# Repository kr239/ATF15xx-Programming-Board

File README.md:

# ATF15xx Programming Board

A simple PCB that will allow you to program 44-pin PLCC ATF15xx series CPLD's using an Byte Blaster or other similar ISP cable.

J2 is the power input, Max 9v DC

# Bill of Materials

-= COMING SOON =-

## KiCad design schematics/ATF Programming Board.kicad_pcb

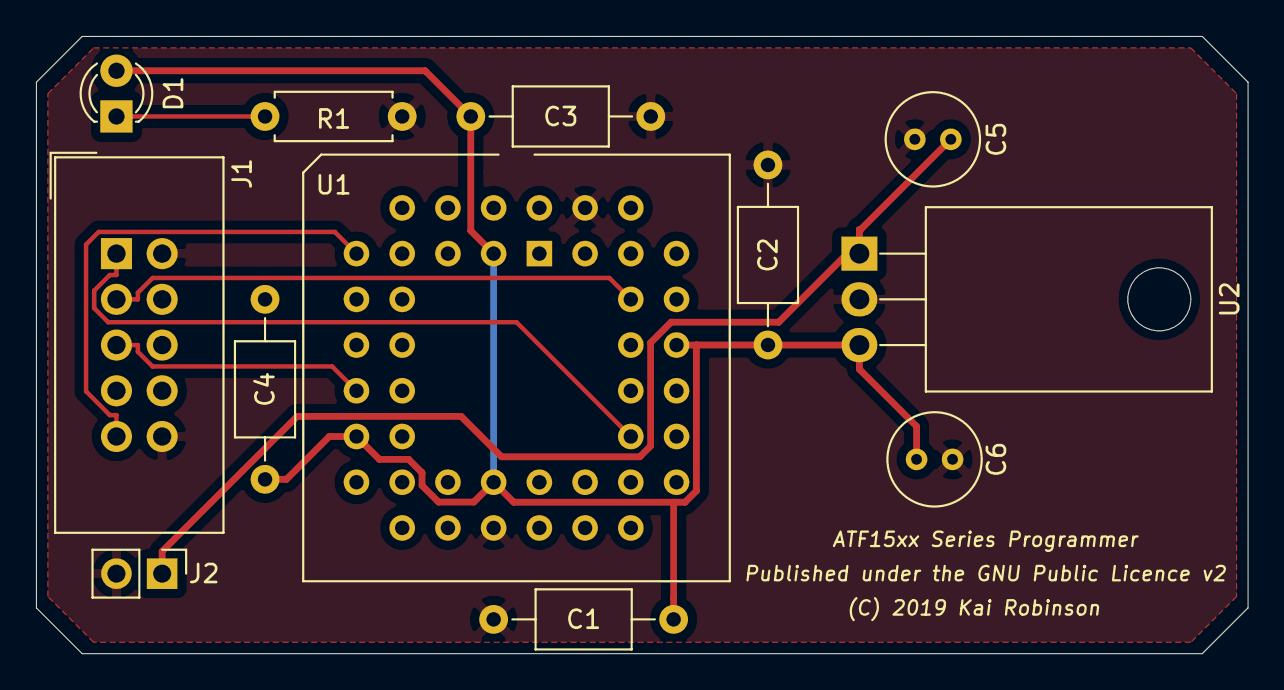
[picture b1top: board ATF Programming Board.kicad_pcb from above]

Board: 2 copper layers, 67.3 x 34.3 mm, 12 parts (0 on the bottom side), 8 nets.

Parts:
C1, C2, C3, C4: 0.1uF; C_Axial_L5.1mm_D3.1mm_P10.00mm_Horizontal
C5: 0.33uF; C_Radial_D5.0mm_H5.0mm_P2.00mm
C6: 0.1uF; C_Radial_D5.0mm_H5.0mm_P2.00mm
D1: LED_ALT; LED_D3.0mm
J1: AVR-JTAG-10; IDC-Header_2x05_P2.54mm_Vertical
J2: Conn_01x02_Male; PinHeader_1x02_P2.54mm_Vertical
R1: 1k; R_Axial_DIN0207_L6.3mm_D2.5mm_P7.62mm_Horizontal
U1: ATF1502ASV-15JU44; PLCC-44_THT-Socket
U2: LM7805_TO220; TO-220-3_Horizontal_TabDown

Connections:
/gnd: C1.1, C2.2, C3.2, C4.1, C5.2, C6.2, J1.2, J1.10, J2.2, R1.1, U1.10, U1.22, U1.30, U1.42, U2.2
/tck: J1.1, U1.32
/tdi: J1.9, U1.7
/tdo: J1.3, U1.38
/tms: J1.5, U1.13
/vcc5: C1.2, C2.1, C3.1, C4.2, C6.1, D1.2, U1.3, U1.15, U1.23, U1.35, U2.3
/vcc_in: C5.1, J2.1, U2.1
unnamed: D1.1, R1.2

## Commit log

2019-06-08 More stuff
    Added renders of the PCB and updated the readme

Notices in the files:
schematics/ATF Programming Board.kicad_pcb:
Published under the GNU Public Licence v2
(C) 2019 Kai Robinson
